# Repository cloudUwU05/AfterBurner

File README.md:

## AfterBurner

This is my backup/posting of my little Afterburner test piece, \
Its not great but i have seen worse

# Testing vid on my youtube [AfterburnerTest](https://youtu.be/r_q5uBkwENI?si=lZsYyg5NFj2jl1zo)

Also some pics

I have used the following Materials:

|          | Steeltube | Acrylictube |  
|----------|----------|----------|
| Outer Diameter   | 6cm  | 6.5cm |
| Length    | 16cm  | 29cm  |
| thickness    |  2.75mm  | 3.6mm  |

The Stl files for the pipeclamps etc are all in the [Stl folder](https://github.com/UwUyourmom/AfterBurner/tree/main/STL) \
The PCB is finally working, i scraped the power part, but the 5V from the ESC controller should be enough

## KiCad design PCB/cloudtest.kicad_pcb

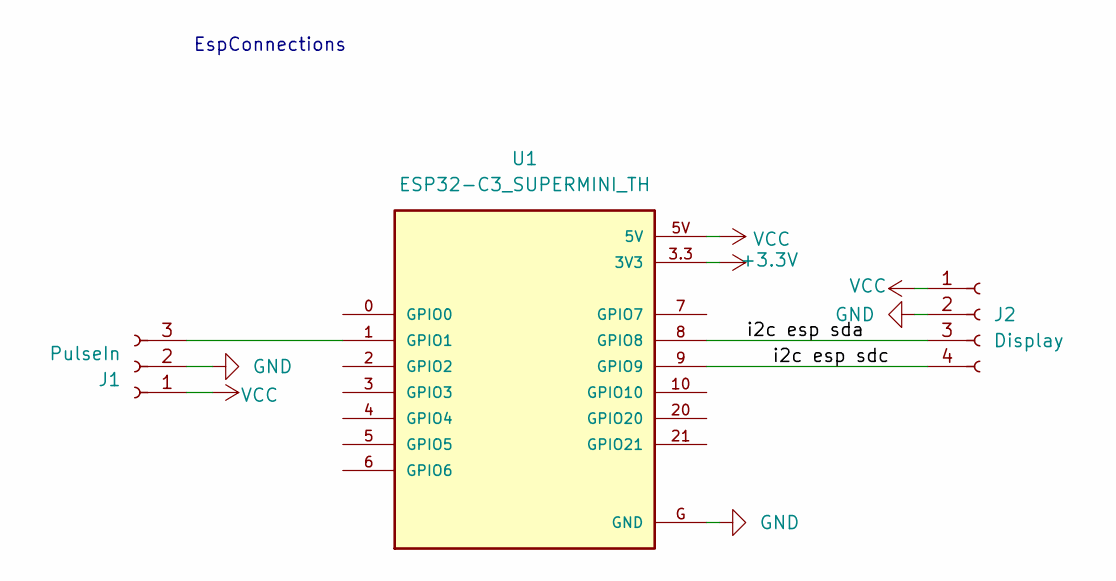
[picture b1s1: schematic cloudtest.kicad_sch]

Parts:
J1: PulseIn; PinHeader_1x03_P2.54mm_Vertical
J2: Display; PinHeader_1x04_P2.54mm_Vertical
U1: ESP32-C3_SUPERMINI_TH; MODULE_ESP32-C3_SUPERMINI

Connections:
+3.3V: U1.3.3 (3V3)
/i2c esp sda: J2.3, U1.8 (GPIO8)
/i2c esp sdc: J2.4, U1.9 (GPIO9)
GND: J1.2, J2.2, U1.G (GND)
unnamed: J1.3, U1.1 (GPIO1)
VCC: J1.1, J2.1, U1.5V

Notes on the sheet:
EspConnections

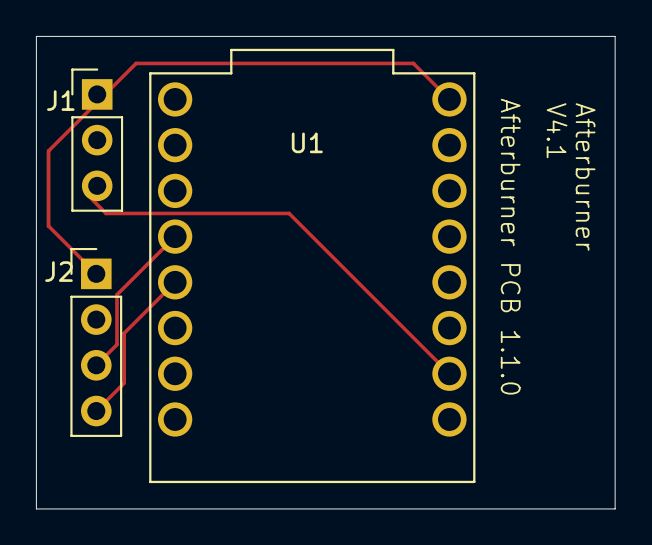
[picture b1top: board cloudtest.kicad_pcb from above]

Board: 2 copper layers, 32.2 x 26.2 mm, 3 parts (0 on the bottom side), 5 nets.

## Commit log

2025-12-08 PCB update, remove power delivery
2025-12-09 PCB update
